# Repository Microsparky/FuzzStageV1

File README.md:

# FuzzStageV1
A modular gain stage for custom fuzz pedal in Eagle

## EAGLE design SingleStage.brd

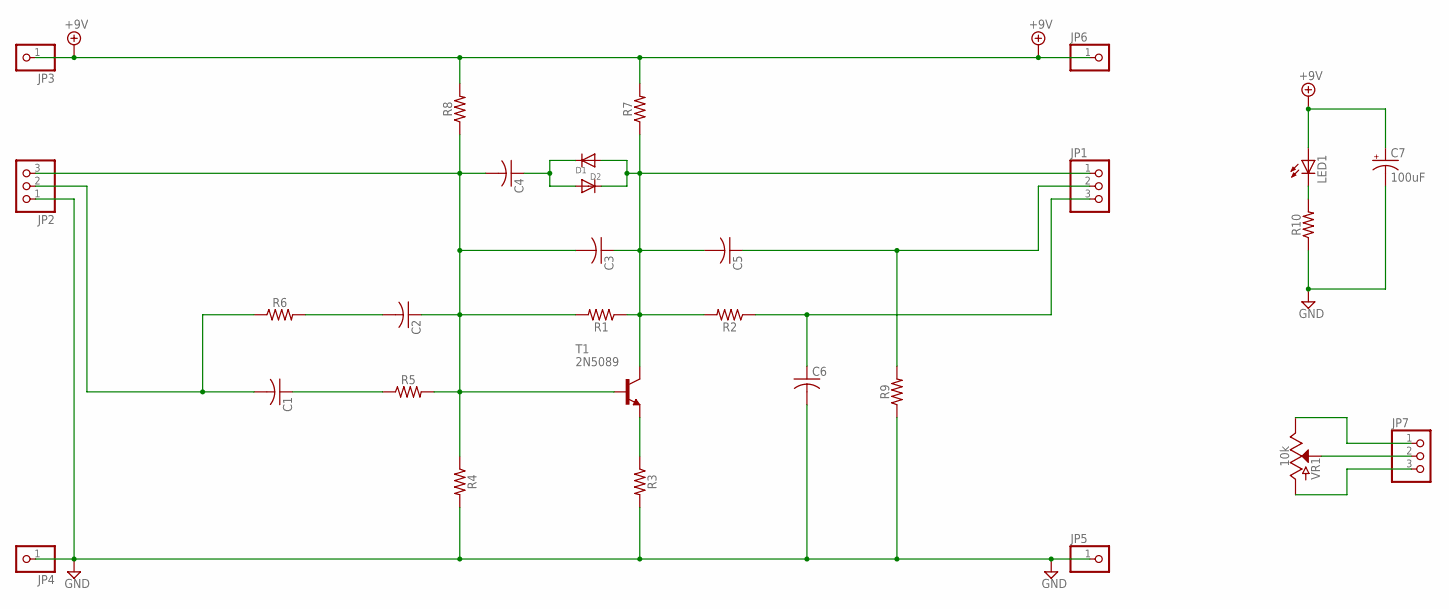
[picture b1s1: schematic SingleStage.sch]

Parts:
C1, C2, C3, C4, C5, C6: C-US050-030X075; C050-030X075
C7: 100uF; CPOL-RADIAL-2.5MM-6.5MM
D1, D2: DIODEDO-1N4148; DO-1N4148
JP1, JP2, JP7: PINHD-1X3CB; 1X03-CLEANBIG
JP3, JP4, JP5, JP6: PINHD-1X1CB; 1X01-CLEANBIG
LED1: LED5MM
R1, R2, R3, R4, R5, R6, R7, R8, R9, R10: AXIAL-0.3
T1: 2N5089; TO92
VR1: 10k; POT-PTH-ALPS

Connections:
+9V: C7.1 (+), JP3.1, JP6.1, LED1.A, R7.P$2 (2), R8.P$2 (2)
GND: C6.2, C7.2 (-), JP2.1, JP4.1, JP5.1, R3.P$2 (2), R4.P$2 (2), R9.P$1 (1), R10.P$1 (1)
unnamed: C2.2, R6.P$2 (2)
unnamed: C1.1, R5.P$1 (1)
unnamed: R3.P$1 (1), T1.3 (E)
unnamed: C2.1, C3.2, C4.2, JP2.3, R1.P$2 (2), R4.P$1 (1), R5.P$2 (2), R8.P$1 (1), T1.2 (B)
unnamed: C4.1, D1.A, D2.C
unnamed: C3.1, C5.2, D1.C, D2.A, JP1.1, R1.P$1 (1), R2.P$2 (2), R7.P$1 (1), T1.1 (C)
unnamed: C1.2, JP2.2, R6.P$1 (1)
unnamed: C5.1, JP1.2, R9.P$2 (2)
unnamed: C6.1, JP1.3, R2.P$1 (1)
unnamed: JP7.1, VR1.P$1 (E)
unnamed: JP7.2, VR1.P$2 (S)
unnamed: LED1.K (C), R10.P$2 (2)
unnamed: JP7.3, VR1.P$3 (A)

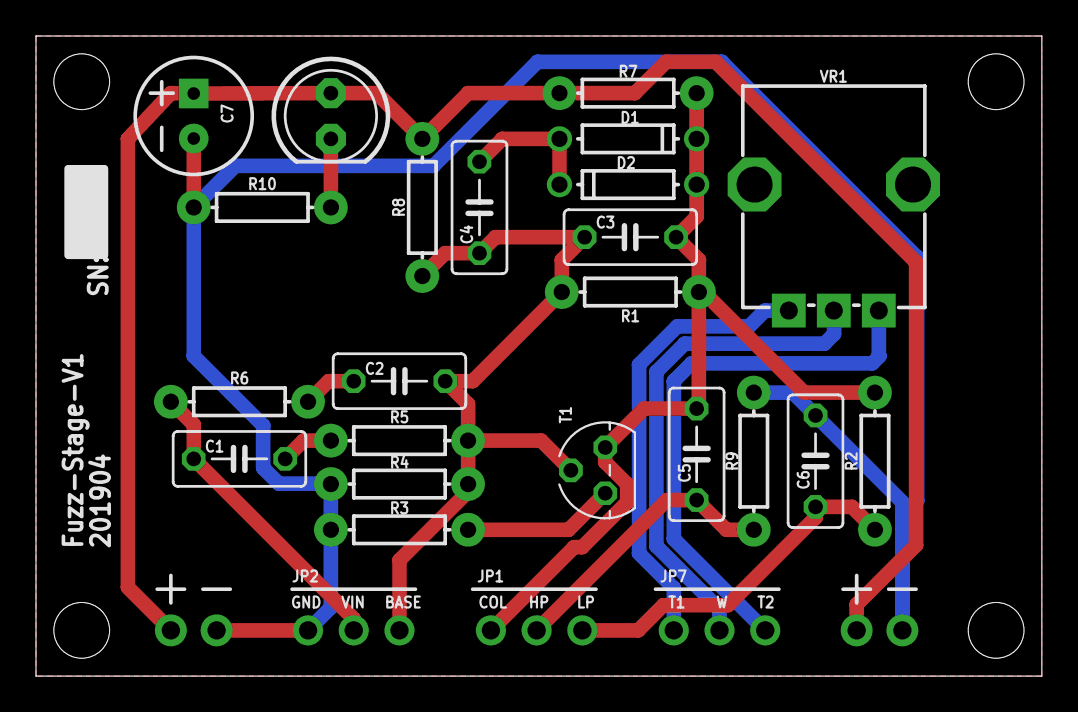
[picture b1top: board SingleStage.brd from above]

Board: 2 copper layers, 55.9 x 35.6 mm, 29 parts (0 on the bottom side), 15 nets.

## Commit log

2019-04-25 Add files via upload
    Initial commit
2019-04-25 Add files via upload
    2-Layer board routed
2019-04-27 Add files via upload
    Layout complete ad Gerber files generated.
2019-04-27 Add files via upload
    adding Gerbers and NCDrill
2019-05-03 Add files via upload
    Prints

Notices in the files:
parts and their libraries:
SparkFun-Capacitors: Licensing: Creative Commons ShareAlike 4.0 International - https://creativecommons.org/licenses/by-sa/4.0
